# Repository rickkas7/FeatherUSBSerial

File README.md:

# Feather USB Serial
*FT232 USB serial port connection to RX/TX (Serial1) in an Adafruit FeatherWing form-factor*

This simple board allows easy access to Serial1, typically for debugging purposes. You insert it in a [Adafruit FeatherWing Doubler](https://www.adafruit.com/product/2890) or [Tripler](https://www.adafruit.com/product/3417) along with your device.

While it's no big deal to attach a [FT232 breakout](https://www.sparkfun.com/products/12731), the FeatherWing is nice and neat with no dangling wires.

This post has all of the information you need to build your own. It's not available for purchase pre-built.

## What You Need

This is a somewhat advanced project mainly because the FT232 has a lot of pins, very close together. It's probably not practical to solder by hand, so you'll need a SMD reflow oven to do it effectively.

- Circuit boards (I order them from [OshPark](https://oshpark.com))
- Stencil (this board can be assembled without one, but I order them from [OshStencils](https://oshstencils.com))
- Solder paste
- Reflow oven (the inexpensive [T962](https://www.amazon.com/dp/B01LZYEF90/ref=dp_prsubs_1) works fine)
- Soldering iron (for the header pins)
- Regular solder

In the eagle directory are the .brd and .sch files for Eagle CAD. One of the reasons I like OshPark is that they accept the .brd files directly, instead of having to generate Gerber files. It costs US$9.00 with free shipping for 3 FeatherWing boards.

There's also a .lbr file with all of the parts in this project.

## BOM (Bill of Materials)

| Quantity | Item | Example |
| --- | --- | --- |
| 1 | 0.01 uF capacitor 0603 | [Murata GCM188R72A103KA37J](https://www.digikey.com/product-detail/en/murata-electronics-north-america/GCM188R72A103KA37J/490-8028-1-ND/4380313) |
| 2 | 0.1 uF capacitor 0603 | [Murata GRM188R71C104KA01D](https://www.digikey.com/product-detail/en/murata-electronics-north-america/GRM188R71C104KA01D/490-1532-1-ND/587771) |
| 1 | 4.7 uF capacitor 0603 | [Murata GRM188R60J475KE19J](https://www.digikey.com/product-detail/en/murata-electronics-north-america/GRM188R60J475KE19J/490-6407-1-ND/3845604) |
| 1 | Ferrite Bead 40 ohm 0805 | [Laird MI0805K400R-10](https://www.digikey.com/products/en/filters/ferrite-beads-and-chips/841?k=MI0805K400R&k=&pkeyword=MI0805K400R&sv=0&pv7=2&pv1989=0&sf=0&quantity=&ColumnSort=0&page=1&pageSize=25) |
| 3 | 680 ohm resistor 1/8w 0805 | [Panasonic ERJ-6GEYJ681V](https://www.digikey.com/product-detail/en/panasonic-electronic-components/ERJ-6GEYJ681V/P680ACT-ND/90033) | 
| 2 | LED red 5mA 0603 | [Lite-On LTST-C193KRKT-5A](https://www.digikey.com/product-detail/en/lite-on-inc/LTST-C193KRKT-5A/160-1830-1-ND/2356251) |
| 1 | LED green 5mA 0603 | [Lite-On LTST-C193KGKT-5A](https://www.digikey.com/product-detail/en/lite-on-inc/LTST-C193KGKT-5A/160-1828-1-ND/2356247) |
| 1 | FT232RL USB serial | [FTDI FT232RL](https://www.digikey.com/product-detail/en/ftdi-future-technology-devices-international-ltd/FT232RL-REEL/768-1007-1-ND/1836402) |
| 1 | Micro USB B SMD | [Amphenol FCI 10118194-0001LF](https://www.digikey.com/products/en?keywords=609-4618-1-nd) |
| | Male header pins 0.1" | [Sullins PRPC040SAAN-RC](https://www.digikey.com/product-detail/en/PRPC040SAAN-RC/S1011EC-40-ND/2775214) |

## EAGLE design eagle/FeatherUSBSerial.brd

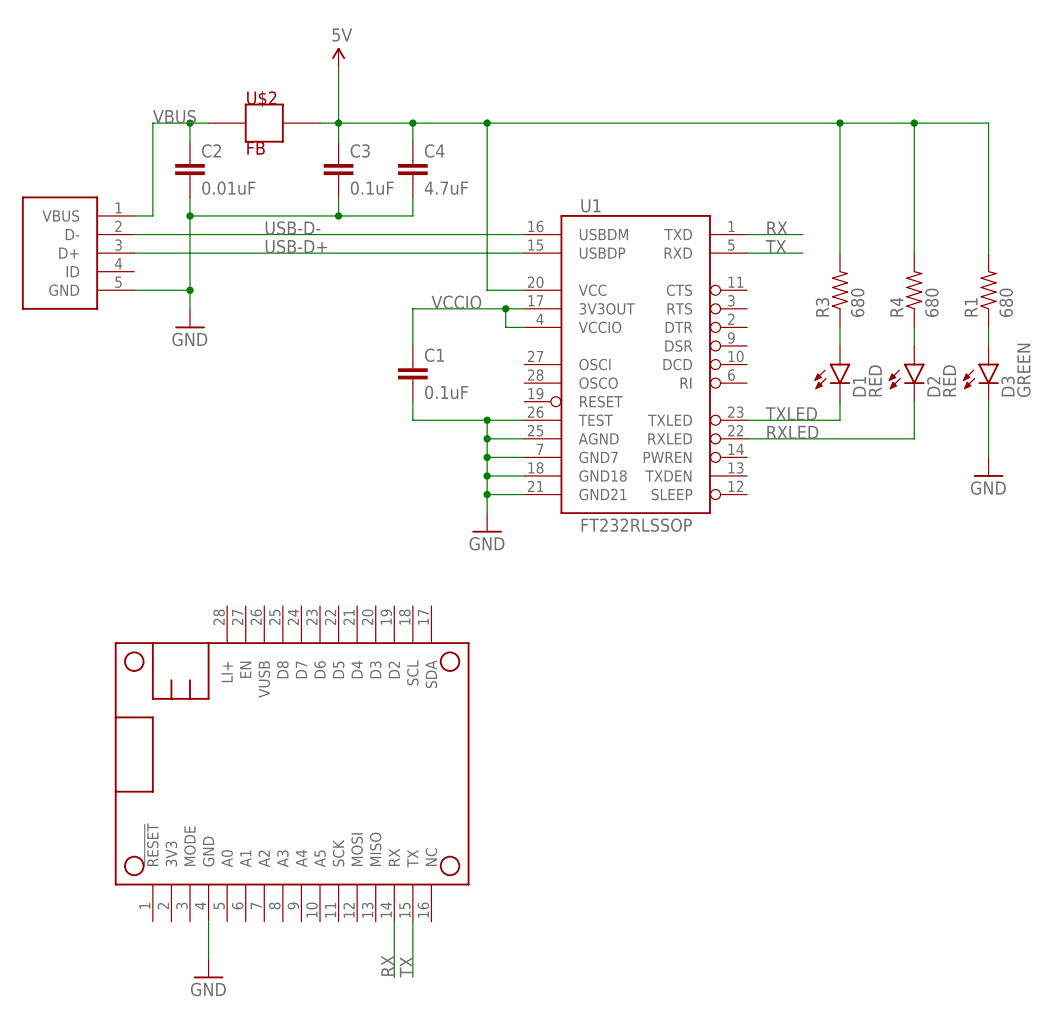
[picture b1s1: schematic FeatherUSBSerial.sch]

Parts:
C1, C3: 0.1uF; 0603-CAP
C2: 0.01uF; 0603-CAP
C4: 4.7uF; 0603-CAP
D1, D2: RED; LED-0603
D3: GREEN; LED-0603
MS1: FEATHERWING_NODIM
R1, R3, R4: 680; 0805
U1: FT232RLSSOP; SSOP28DB
U$1: USB-MICRO-B-SOCKET-AMPHENOL; USB-B-SMT-AMPHENOL
U$2: FB; 0805

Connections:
5V: C3.1, C4.1, R1.2, R3.2, R4.2, U1.20 (VCC), U$2.2
GND: C1.2, C2.2, C3.2, C4.2, D3.C, MS1.4 (GND), U1.7 (GND7), U1.18 (GND18), U1.21 (GND21), U1.25 (AGND), U1.26 (TEST), U$1.5 (GND)
unnamed: D3.A, R1.1
unnamed: D1.A, R3.1
unnamed: D2.A, R4.1
RX: MS1.14 (RX), U1.1 (TXD)
RXLED: D2.C, U1.22 (RXLED)
TX: MS1.15 (TX), U1.5 (RXD)
TXLED: D1.C, U1.23 (TXLED)
USB-D+: U1.15 (USBDP), U$1.3 (D+)
USB-D-: U1.16 (USBDM), U$1.2 (D-)
VBUS: C2.1, U$1.1 (VBUS), U$2.1
VCCIO: C1.1, U1.4 (VCCIO), U1.17 (3V3OUT)

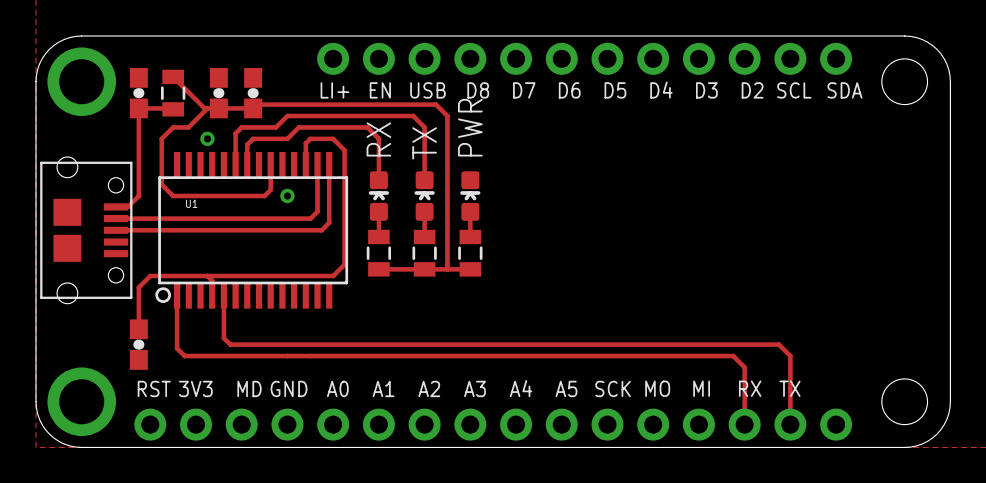
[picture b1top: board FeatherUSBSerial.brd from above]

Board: 2 copper layers, 50.8 x 22.9 mm, 14 parts (0 on the bottom side), 13 nets.

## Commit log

2019-03-01 initial checkin
